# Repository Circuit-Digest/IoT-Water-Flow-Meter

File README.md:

# DIY ESP32-Based Water Flow Meter: Conserve Water, Save the Planet

Water is one of our most precious resources, vital for all forms of life on Earth. Despite its importance, water wastage is a significant issue globally, contributing to water scarcity and environmental degradation. Efficient water management is crucial in addressing this challenge, and technology plays a vital role in it. By monitoring and managing water usage, we can significantly reduce wastage. As a first step in addressing this, we have designed an IoT based water flow meter. It is powered by the ESP32-S3 SoC from Espressif. We have used an ESP32-S3 Wroom 1 module for the project which will be much easier to handle when assembling the PCB. the device itself is battery powered and the custom PCB contains the necessary battery charging circuitry to recharge the internal battery. The battery charging circuit is based on the MAX1898 single-cell battery charger chip from Analog Devices. For powering the ESP32-S3 we have used the ADP1706 ultra low noise LDO, and for the reset circuitry we have used the ADM803 power supervisory chip. We have also included a provision for a 1.28” round TFT display for any future upgrades. The flow meter can be directly attached to the top of the flow sensor.

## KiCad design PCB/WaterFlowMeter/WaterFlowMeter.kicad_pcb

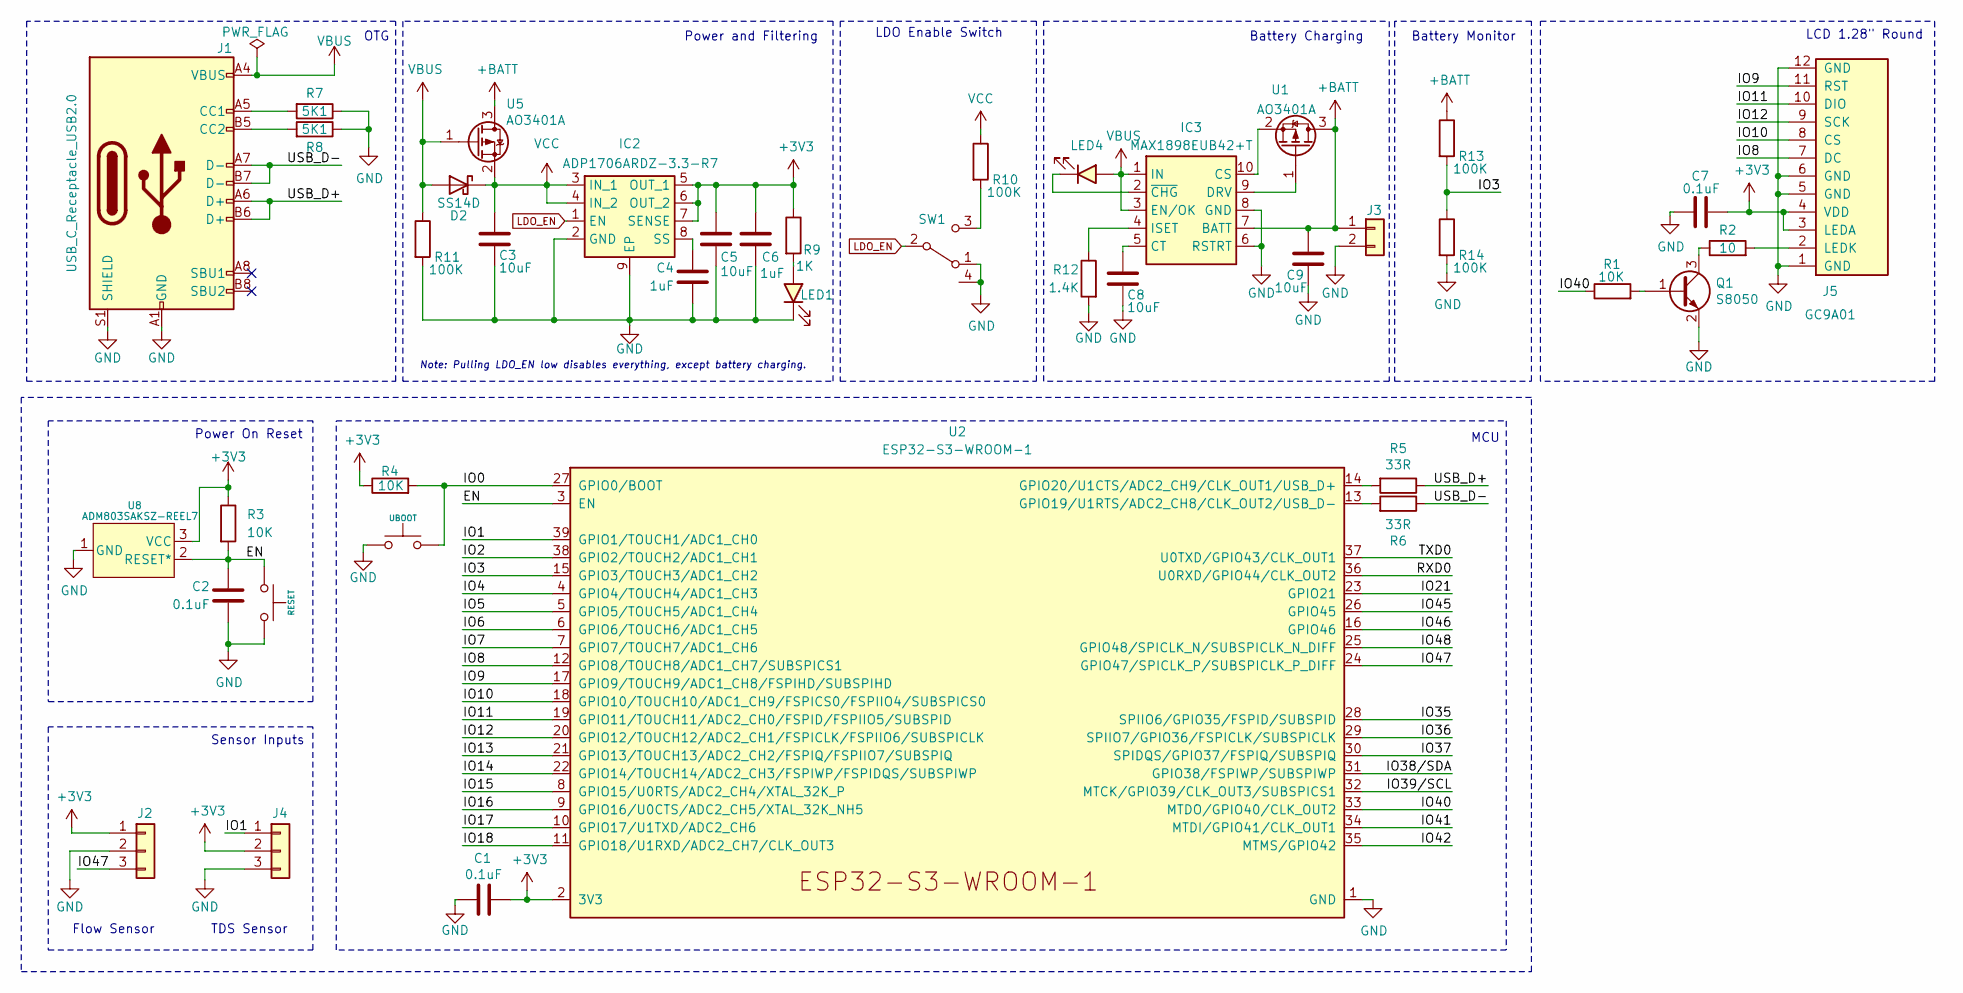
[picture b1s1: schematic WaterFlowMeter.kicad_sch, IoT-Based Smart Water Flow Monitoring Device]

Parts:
BOOT1: UBOOT; Tactile 3x4x2mm TS-A010; DigiKey Part Number 2449-CS1213AGF160CT-ND
BOOT2: RESET; Tactile 3x4x2mm TS-A010; DigiKey Part Number 2449-CS1213AGF160CT-ND
C1, C2, C7: 0.1uF; C_0603_1608Metric; DigiKey Part Number 490-6328-1-ND
C3, C5, C8, C9: 10uF; C_0603_1608Metric; DigiKey Part Number 490-10692-1-ND
C4, C6: 1uF; C_0603_1608Metric; DigiKey Part Number 490-10018-1-ND
D2: SS14D; D_SMA; DigiKey Part Number SS14CT-ND
IC2: ADP1706ARDZ-3.3-R7; SOIC127P600X175-9N; DigiKey Part Number 505-ADP1706ARDZ-3.3-R7CT-ND
IC3: MAX1898EUB42+T; SOP50P490X110-10N; DigiKey Part Number MAX1898EUB42+TCT-ND
J1: USB_C_Receptacle_USB2.0; USB_C_Receptacle_XKB_U262-16XN-4BVC11; DigiKey Part Number 664-12402012E212ACT-ND
J2, J4: Conn_01x03; JST_PH_B3B-PH-K_1x03_P2.00mm_Vertical; DigiKey Part Number A100035-ND
J3: B2B-PH-SM4-TB(LF)(SN); JST_PH_B2B-PH-K_1x02_P2.00mm_Vertical; DigiKey Part Number 455-1704-ND
J5: GC9A01
LED1: LED Red; LED_0603_1608Metric; DigiKey Part Number 3147-B1911USD-20D000114U1930CT-ND
LED4: LED Blue; LED_0603_1608Metric; DigiKey Part Number 3147-B1911NB--20C005314U1930CT-ND
Q1: S8050; SOT-23; DigiKey Part Number MMSS8050-L-TPMSCT-ND
R1, R3, R4: 10K; R_0603_1608Metric; DigiKey Part Number P10.0KHCT-ND
R2: 10; R_0603_1608Metric; DigiKey Part Number P10.0HCT-ND
R5, R6: 33R; R_0603_1608Metric; DigiKey Part Number P17467CT-ND
R7, R8: 5K1; R_0603_1608Metric; DigiKey Part Number P5.10KHCT-ND
R9: 1K; R_0603_1608Metric; DigiKey Part Number P1.00KHCT-ND
R10, R11, R13, R14: 100K; R_0603_1608Metric; DigiKey Part Number P100KHCT-ND
R12: 1.4K; R_0603_1608Metric; DigiKey Part Number P1.40KHCT-ND
SW1: SLW-66527511-SMT-TR; slide switch spdt; DigiKey Part Number 2223-SLW-66527511-SMT-TRCT-ND
U1, U5: AO3401A; SOT-23; DigiKey Part Number AO3401-ND
U2: ESP32-S3-WROOM-1; DigiKey Part Number 1965-ESP32-S3-WROOM-1-N16R8CT-ND
U8: ADM803SAKSZ-REEL7; KS_3_ADI; DigiKey Part Number 505-ADM803SAKSZ-REEL7CT-ND

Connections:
+BATT: C9.1, IC3.7 (BATT), J3.1, R13.1, U1.3 (D), U5.3 (D)
/EN: BOOT2.1, C2.1, R3.2, U2.3 (EN), U8.2 (RESET*)
/IO0: BOOT1.1, R4.2, U2.27 (GPIO0/BOOT)
/IO1: J4.1, U2.39 (GPIO1/TOUCH1/ADC1_CH0)
/IO2: U2.38 (GPIO2/TOUCH2/ADC1_CH1)
/IO3: R13.2, R14.1, U2.15 (GPIO3/TOUCH3/ADC1_CH2)
/IO4: U2.4 (GPIO4/TOUCH4/ADC1_CH3)
/IO5: U2.5 (GPIO5/TOUCH5/ADC1_CH4)
/IO6: U2.6 (GPIO6/TOUCH6/ADC1_CH5)
/IO7: U2.7 (GPIO7/TOUCH7/ADC1_CH6)
/IO8: J5.7 (DC), U2.12 (GPIO8/TOUCH8/ADC1_CH7/SUBSPICS1)
/IO9: J5.11 (RST), U2.17 (GPIO9/TOUCH9/ADC1_CH8/FSPIHD/SUBSPIHD)
/IO10: J5.8 (CS), U2.18 (GPIO10/TOUCH10/ADC1_CH9/FSPICS0/FSPIIO4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)
/IO11: J5.10 (DIO), U2.19 (GPIO11/TOUCH11/ADC2_CH0/FSPID/FSPIIO5/S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)
/IO12: J5.9 (SCK), U2.20 (GPIO12/TOUCH12/ADC2_CH1/FSPICLK/FSPIIO6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)
/IO13: U2.21 (GPIO13/TOUCH13/ADC2_CH2/FSPIQ/FSPIIO7/S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)
/IO14: U2.22 (GPIO14/TOUCH14/ADC2_CH3/FSPIWP/FSPIDQS/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)
/IO15: U2.8 (GPIO15/U0RTS/ADC2_CH4/XTAL_32K_P)
/IO16: U2.9 (GPIO16/U0CTS/ADC2_CH5/XTAL_32K_NH5)
/IO17: U2.10 (GPIO17/U1TXD/ADC2_CH6)
/IO18: U2.11 (GPIO18/U1RXD/ADC2_CH7/CLK_OUT3)
/IO21: U2.23 (GPIO21)
/IO35: U2.28 (SPIIO6/GPIO35/FSPID/SUBSPID)
/IO36: U2.29 (SPIIO7/GPIO36/FSPICLK/SUBSPICLK)
/IO37: U2.30 (SPIDQS/GPIO37/FSPIQ/SUBSPIQ)
/IO38/SDA: U2.31 (GPIO38/FSPIWP/SUBSPIWP)
/IO39/SCL: U2.32 (MTCK/GPIO39/CLK_OUT3/SUBSPICS1)
/IO40: R1.1, U2.33 (MTDO/GPIO40/CLK_OUT2)
/IO41: U2.34 (MTDI/GPIO41/CLK_OUT1)
/IO42: U2.35 (MTMS/GPIO42)
/IO45: U2.26 (GPIO45)
/IO46: U2.16 (GPIO46)
/IO47: J2.3, U2.24 (GPIO47/SPICLK_P/SUBSPICLK_P_DIFF)
/IO48: U2.25 (GPIO48/SPICLK_N/SUBSPICLK_N_DIFF)
/RXD0: U2.36 (U0RXD/GPIO44/CLK_OUT2)
/TXD0: U2.37 (U0TXD/GPIO43/CLK_OUT1)
/USB_D+: J1.A6 (D+), J1.B6 (D+), R5.1
/USB_D-: J1.A7 (D-), J1.B7 (D-), R6.1
LDO_EN: IC2.1 (EN), SW1.2 (B)
unnamed: C4.1, IC2.8 (SS)
unnamed: IC3.10 (CS), U1.2 (S)
unnamed: C8.1, IC3.5 (CT)
unnamed: IC3.9 (DRV), U1.1 (G)
unnamed: IC3.4 (ISET), R12.1
unnamed: IC3.2 (~CHG), LED4.1 (K)
unnamed: J1.A5 (CC1), R7.2
unnamed: J1.B5 (CC2), R8.2
unnamed: J5.2 (LEDK), R2.2
unnamed: LED1.2 (A), R9.2
unnamed: Q1.3 (C), R2.1
unnamed: Q1.1 (E), R1.2
unnamed: R10.2, SW1.3 (C)
unnamed: R6.2, U2.13 (GPIO19/U1RTS/ADC2_CH8/CLK_OUT2/USB_D-)
unnamed: R5.2, U2.14 (GPIO20/U1CTS/ADC2_CH9/CLK_OUT1/USB_D+)
VBUS: D2.2 (A), IC3.1 (IN), IC3.3 (EN/OK), J1.A4 (VBUS), J1.A9 (VBUS), J1.B4 (VBUS), J1.B9 (VBUS), LED4.2 (A), R11.1, U5.1 (G)
VCC: C3.1, D2.1 (K), IC2.3 (IN_1), IC2.4 (IN_2), R10.1, U5.2 (S)

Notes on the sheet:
OTG
TDS Sensor
Note: Pulling LDO_EN low disables everything, except battery charging.
Sensor Inputs
Power On Reset
Battery Charging
MCU
LCD 1.28" Round
LDO Enable Switch
Battery Monitor
Flow Sensor
Power and Filtering

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
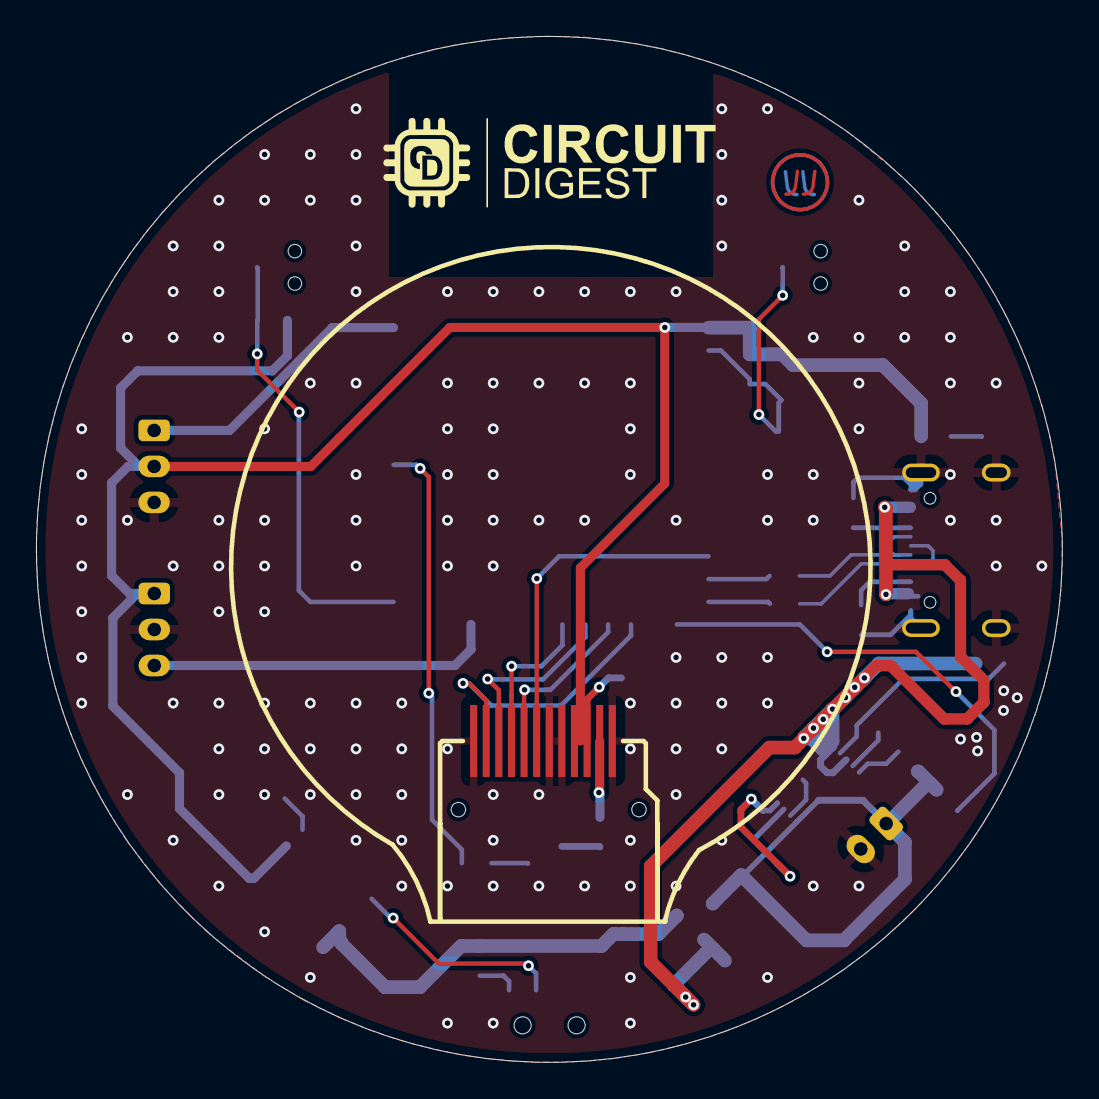
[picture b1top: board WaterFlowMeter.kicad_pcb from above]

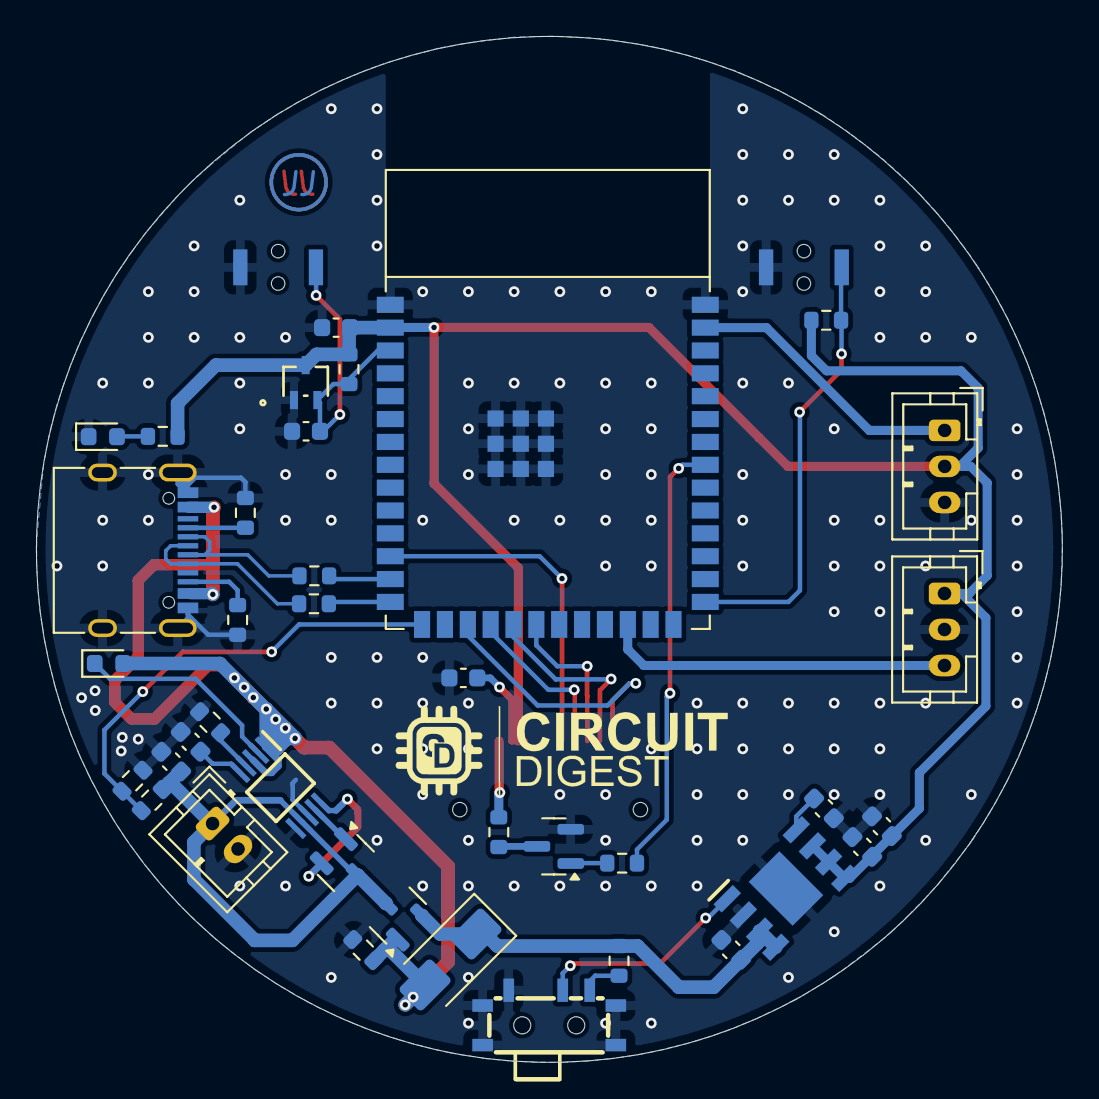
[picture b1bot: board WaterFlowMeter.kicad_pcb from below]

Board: 2 copper layers, 57.0 x 57.0 mm, 41 parts (40 on the bottom side), 34 nets.

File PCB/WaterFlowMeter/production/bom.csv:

Designator,Footprint,Quantity,Value,LCSC Part #
BOOT1,Tactile 3x4x2mm TS-A010,1,UBOOT,
BOOT2,Tactile 3x4x2mm TS-A010,1,RESET,
"C1, C2, C7",0603,3,0.1uF,
"C3, C5, C8, C9",0603,4,10uF,
"C4, C6",0603,2,1uF,
D2,D_SMA,1,SS14D,
IC2,SOIC127P600X175-9N,1,ADP1706ARDZ-3.3-R7,
IC3,SOP50P490X110-10N,1,MAX1898EUB42+T,
J1,USB_C_Receptacle_XKB_U262-16XN-4BVC11,1,USB_C_Receptacle_USB2.0,
"J2, J4",JST_PH_B3B-PH-K_1x03_P2.00mm_Vertical,2,Conn_01x03,
J3,JST_PH_B2B-PH-K_1x02_P2.00mm_Vertical,1, B2B-PH-SM4-TB(LF)(SN) ,
J5,GC9A01,1,GC9A01,
LED1,0603,1,LED Red,
LED4,0603,1,LED Blue,
Q1,SOT-23,1,S8050,
"R1, R3, R4",0603,3,10K,
"R10, R11, R13, R14",0603,4,100K,
R12,0603,1,1.4K,
R2,0603,1,10,
"R5, R6",0603,2,33R,
"R7, R8",0603,2,5K1,
R9,0603,1,1K,
SW1,slide switch spdt,1,SLW-66527511-SMT-TR,
"U1, U5",SOT-23,2,AO3401A,
U2,ESP32-S3-WROOM-1,1,ESP32-S3-WROOM-1,
U8,KS_3_ADI,1,ADM803SAKSZ-REEL7,
